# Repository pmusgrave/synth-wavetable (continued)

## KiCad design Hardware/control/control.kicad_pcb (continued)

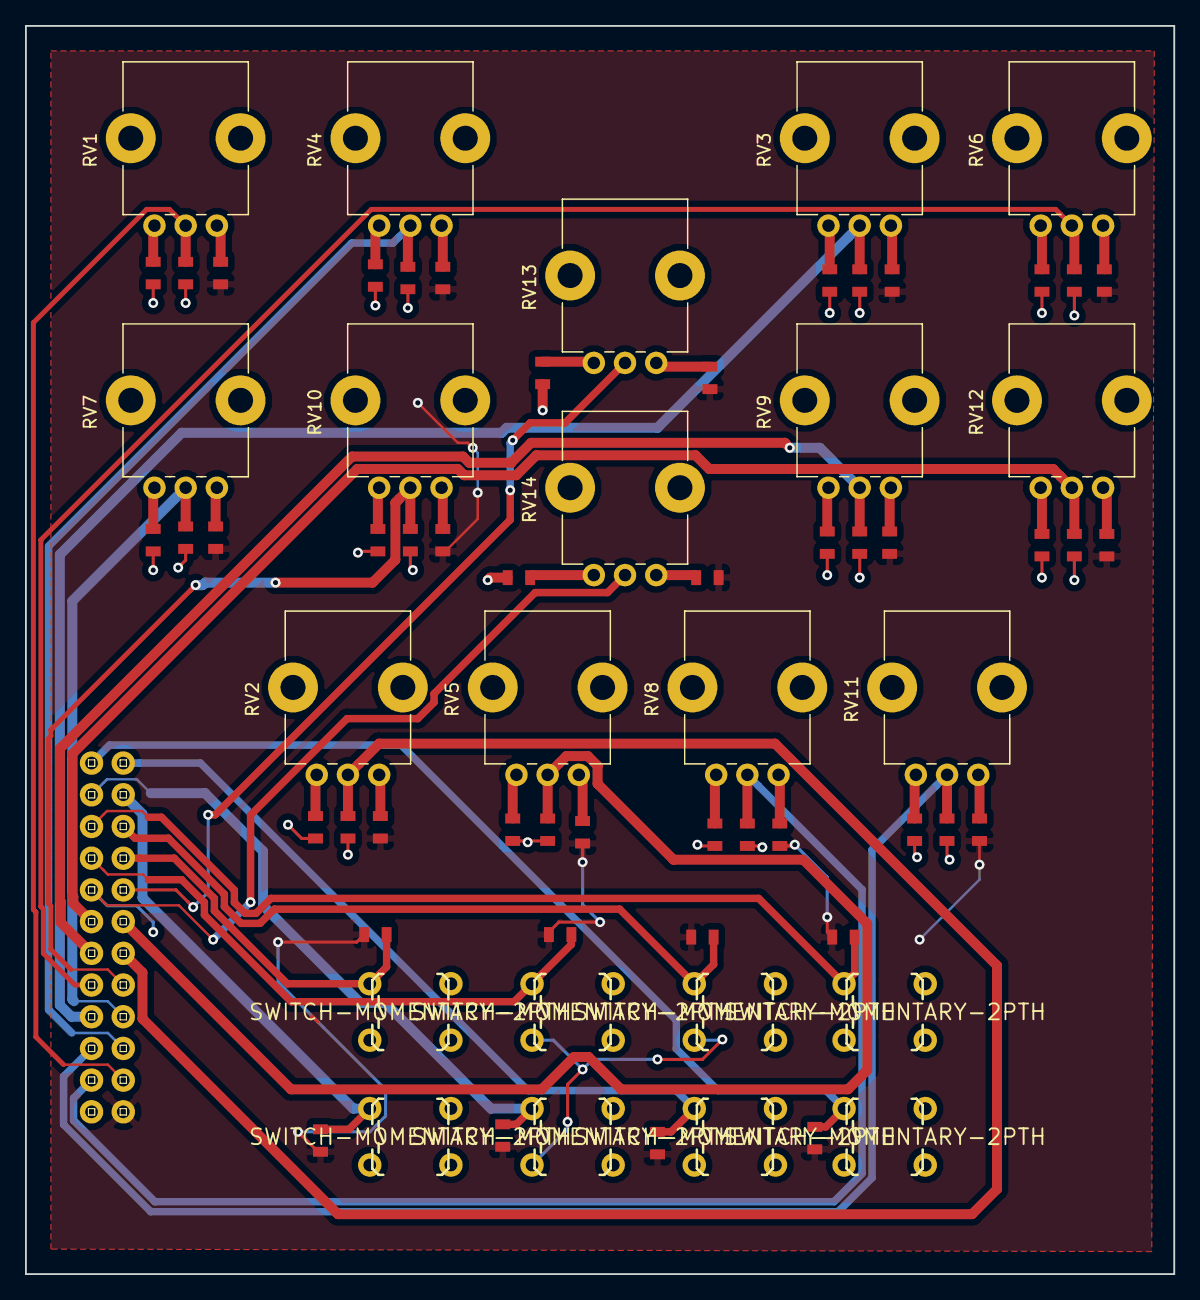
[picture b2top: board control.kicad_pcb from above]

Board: 2 copper layers, 92.0 x 100.0 mm, 71 parts (0 on the bottom side), 52 nets.

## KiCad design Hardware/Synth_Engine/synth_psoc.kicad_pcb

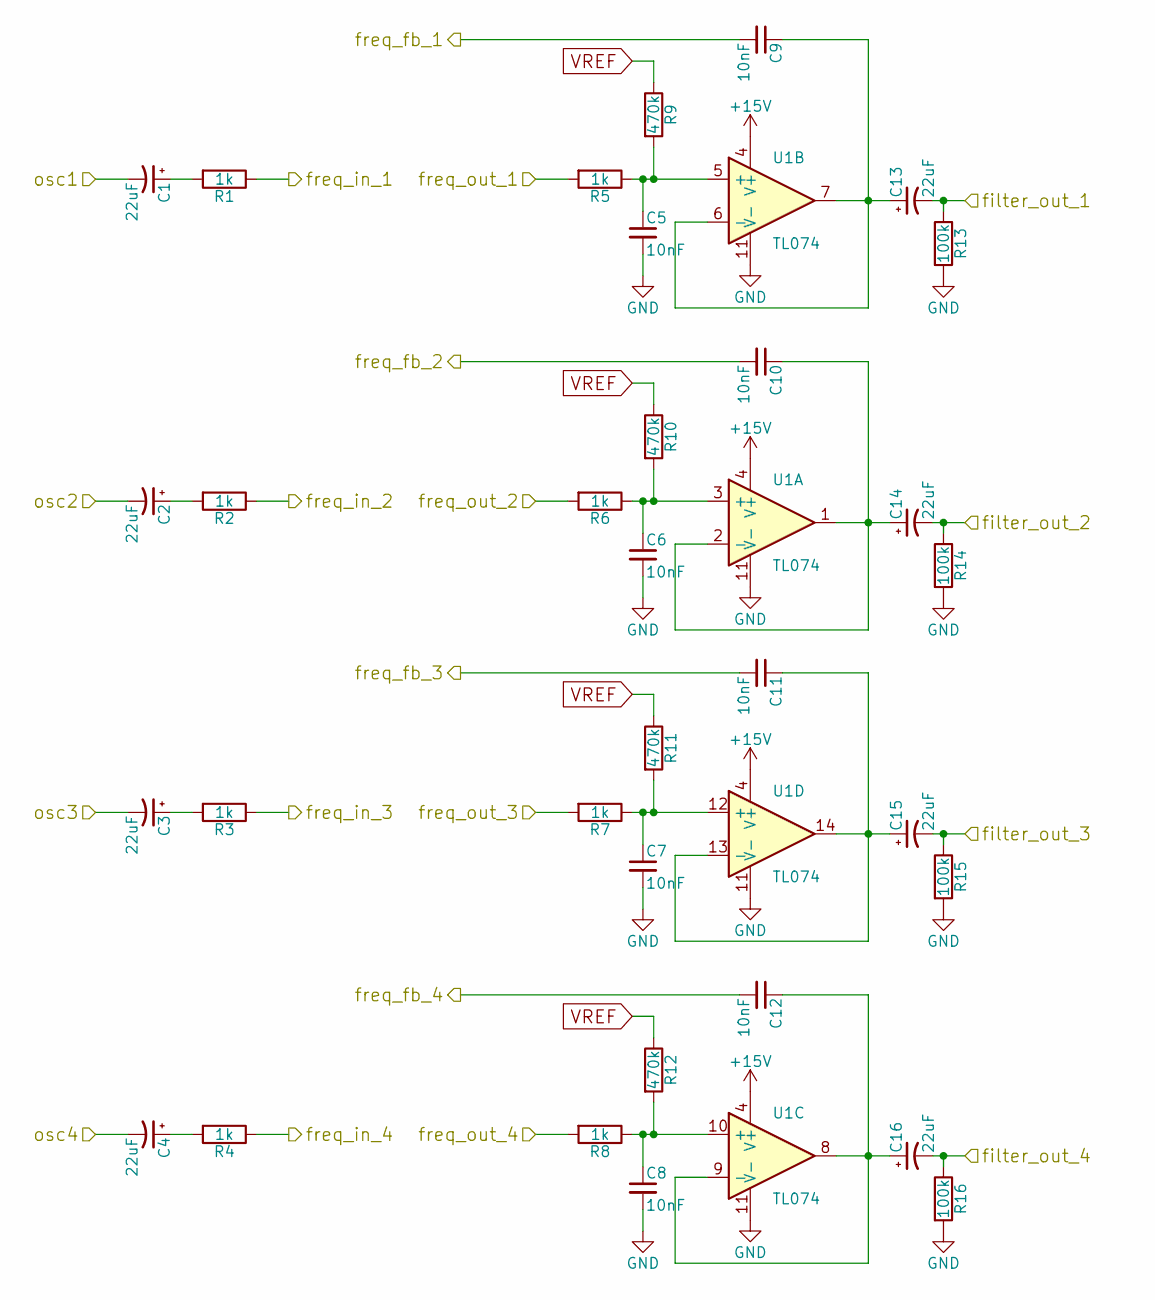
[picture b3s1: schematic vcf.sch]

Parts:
C1, C2, C3, C4, C13, C14, C15, C16: 22uF; CP_Elec_5x5.7
C5, C6, C7, C8, C9, C10, C11, C12: 10nF; 0805
R1, R2, R3, R4, R5, R6, R7, R8: 1k; 0805
R9, R10, R11, R12: 470k; 0805
R13, R14, R15, R16: 100k; 0805
U1: TL074; SOIC-14_W3.9mm

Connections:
+15V: U1.4 (V+); also elsewhere on the board
/Connectors/freq_fb_1: C9.2; also elsewhere on the board
/Connectors/freq_fb_2: C10.2; also elsewhere on the board
/Connectors/freq_fb_3: C11.2; also elsewhere on the board
/Connectors/freq_fb_4: C12.2; also elsewhere on the board
/Connectors/freq_in_1: R1.1; also elsewhere on the board
/Connectors/freq_in_2: R2.1; also elsewhere on the board
/Connectors/freq_in_3: R3.1; also elsewhere on the board
/Connectors/freq_in_4: R4.1; also elsewhere on the board
/Connectors/freq_out_1: R5.2; also elsewhere on the board
/Connectors/freq_out_2: R6.2; also elsewhere on the board
/Connectors/freq_out_3: R7.2; also elsewhere on the board
/Connectors/freq_out_4: R8.2; also elsewhere on the board
/Filters/filter_out_1: C13.2, R13.1; also elsewhere on the board
/Filters/filter_out_2: C14.2, R14.1; also elsewhere on the board
/Filters/filter_out_3: C15.2, R15.1; also elsewhere on the board
/Filters/filter_out_4: C16.2, R16.1; also elsewhere on the board
/Filters/osc1: C1.2; also elsewhere on the board
/Filters/osc2: C2.2; also elsewhere on the board
/Filters/osc3: C3.2; also elsewhere on the board
/Filters/osc4: C4.2; also elsewhere on the board
GND: C5.2, C6.2, C7.2, C8.2, R13.2, R14.2, R15.2, R16.2, U1.11 (V-); also elsewhere on the board
unnamed: C1.1, R1.2
unnamed: C2.1, R2.2
unnamed: C3.1, R3.2
unnamed: C4.1, R4.2
unnamed: C5.1, R5.1, R9.2, U1.5 (+)
unnamed: C6.1, R6.1, R10.2, U1.3 (+)
unnamed: C7.1, R7.1, R11.2, U1.12 (+)
unnamed: C8.1, R8.1, R12.2, U1.10 (+)
unnamed: C10.1, C14.1, U1.1, U1.2 (-)
unnamed: C11.1, C15.1, U1.13 (-), U1.14
unnamed: C12.1, C16.1, U1.8, U1.9 (-)
unnamed: C9.1, C13.1, U1.6 (-), U1.7
VREF: R9.1, R10.1, R11.1, R12.1; also elsewhere on the board

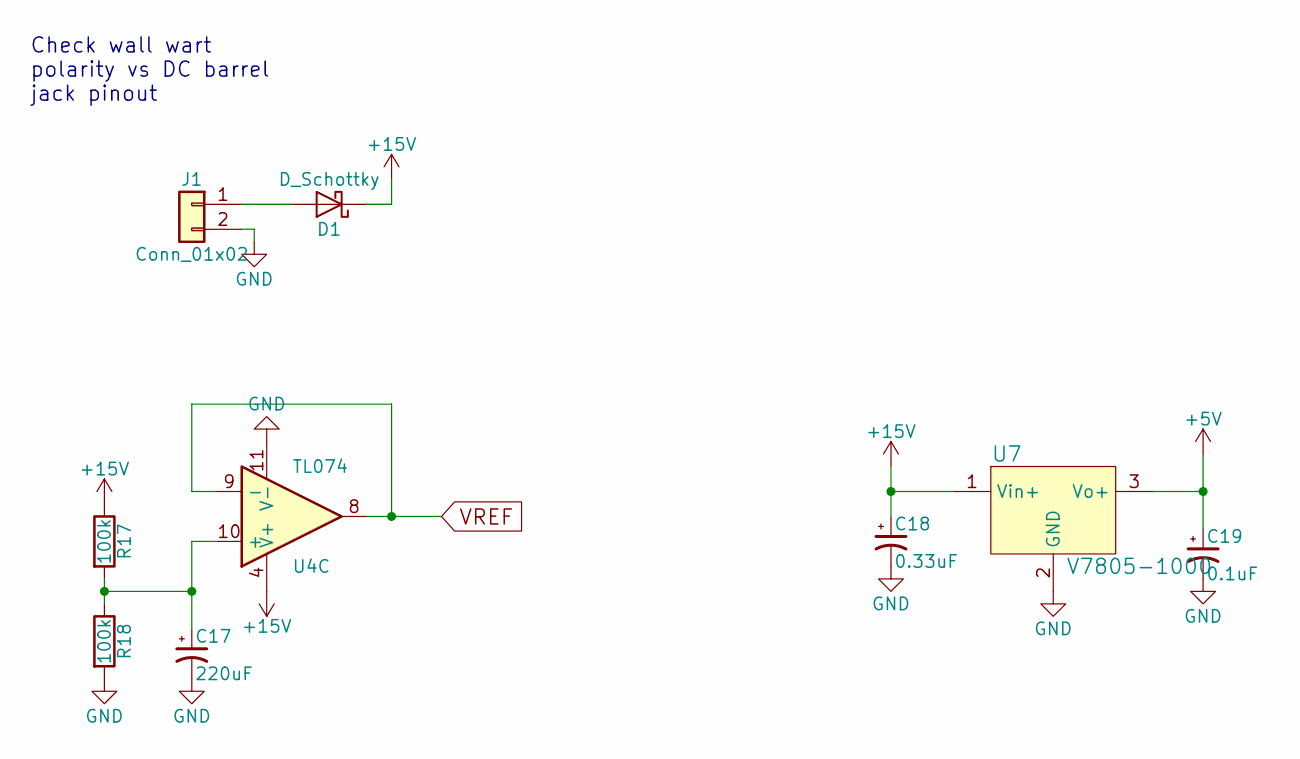
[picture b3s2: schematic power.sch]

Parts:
C17: 220uF; CP_Elec_8x10
C18: 0.33uF; 0805
C19: 0.1uF; 0805
D1: D_Schottky; D_SMB
J1: Conn_01x02; Pin_Header_Straight_1x02_Pitch2.00mm
R17, R18: 100k; 0805
U4: TL074; SOIC-14_W3.9mm
U7: V7805-1000; 3-SIP_Module_V7805-1000; MPN V7805-1000; Digi-Key_PN 102-1715-ND

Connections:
+5V: C19.1, U7.3 (Vo+); also elsewhere on the board
+15V: C18.1, D1.1 (K), R17.1, U4.4 (V+), U7.1 (Vin+); also elsewhere on the board
GND: C17.2, C18.2, C19.2, J1.2, R18.2, U4.11 (V-), U7.2 (GND); also elsewhere on the board
unnamed: C17.1, R17.2, R18.1, U4.10 (+)
unnamed: D1.2 (A), J1.1
VREF: U4.8, U4.9 (-); also elsewhere on the board

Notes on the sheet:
Check wall wart polarity vs DC barrel jack pinout

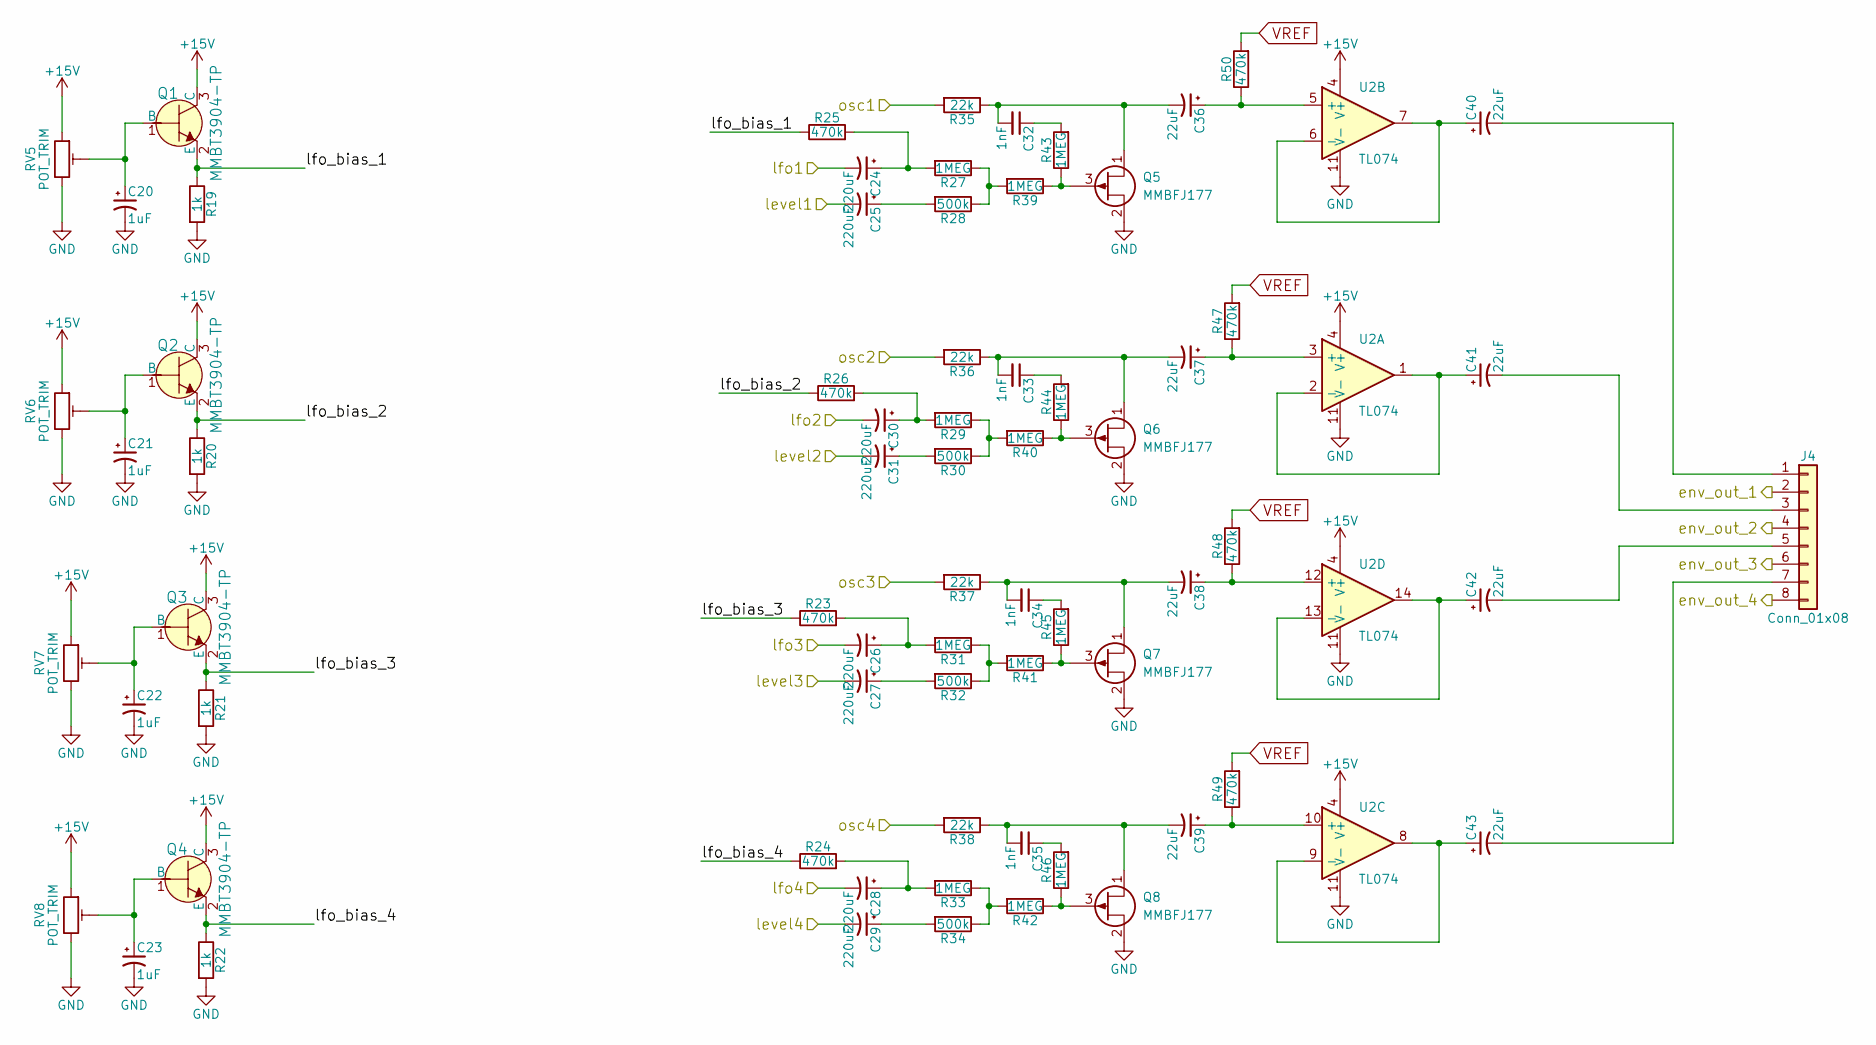
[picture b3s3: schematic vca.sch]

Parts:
C20, C21, C22, C23: 1uF; CP_Elec_4x4.5
C24, C25, C26, C27, C28, C29, C30, C31: 220uF; CP_Elec_8x10
C32, C33, C34, C35: 1nF; 0805
C36, C37, C38, C39, C40, C41, C42, C43: 22uF; CP_Elec_5x5.7
J4: Conn_01x08; Pin_Header_Straight_1x08_Pitch2.54mm
Q1, Q2, Q3, Q4: MMBT3904-TP; SOT-23-3; MPN MMBT3904-TP; Digi-Key_PN MMBT3904TPMSCT-ND
Q5, Q6, Q7, Q8: MMBFJ177; SOT-23-3
R19, R20, R21, R22: 1k; 0805
R23, R24, R25, R26, R47, R48, R49, R50: 470k; 0805
R27, R29, R31, R33, R39, R40, R41, R42, R43, R44, R45, R46: 1MEG; 0805
R28, R30, R32, R34: 500k; 0805
R35, R36, R37, R38: 22k; 0805
RV5, RV6, RV7, RV8: POT_TRIM; Potentiometer_Trimmer-EVM3E
U2: TL074; SOIC-14_W3.9mm

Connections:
+15V: Q1.3 (C), Q2.3 (C), Q3.3 (C), Q4.3 (C), RV5.1, RV6.1, RV7.1, RV8.1, U2.4 (V+); also elsewhere on the board
/Envelope/env_out_1: J4.2; also elsewhere on the board
/Envelope/env_out_2: J4.4; also elsewhere on the board
/Envelope/env_out_3: J4.6; also elsewhere on the board
/Envelope/env_out_4: J4.8; also elsewhere on the board
/Envelope/lfo_bias_1: Q1.2 (E), R19.1, R25.1
/Envelope/lfo_bias_2: Q2.2 (E), R20.1, R26.1
/Envelope/lfo_bias_3: Q3.2 (E), R21.1, R23.1
/Envelope/lfo_bias_4: Q4.2 (E), R22.1, R24.1
/Filters/filter_out_1: R35.2; also elsewhere on the board
/Filters/filter_out_2: R36.2; also elsewhere on the board
/Filters/filter_out_3: R37.2; also elsewhere on the board
/Filters/filter_out_4: R38.2; also elsewhere on the board
/Microcontroller/envelope_pwm_1: C25.2; also elsewhere on the board
/Microcontroller/envelope_pwm_2: C31.2; also elsewhere on the board
/Microcontroller/envelope_pwm_3: C27.2; also elsewhere on the board
/Microcontroller/envelope_pwm_4: C29.2; also elsewhere on the board
/lfo_out_1: C24.2; also elsewhere on the board
/lfo_out_2: C30.2; also elsewhere on the board
/lfo_out_3: C26.2; also elsewhere on the board
/lfo_out_4: C28.2; also elsewhere on the board
GND: C20.2, C21.2, C22.2, C23.2, Q5.2 (S), Q6.2 (S), Q7.2 (S), Q8.2 (S), R19.2, R20.2, R21.2, R22.2, RV5.3, RV6.3, RV7.3, RV8.3, U2.11 (V-); also elsewhere on the board
unnamed: C20.1, Q1.1 (B), RV5.2
unnamed: C21.1, Q2.1 (B), RV6.2
unnamed: C22.1, Q3.1 (B), RV7.2
unnamed: C23.1, Q4.1 (B), RV8.2
unnamed: C24.1, R25.2, R27.2
unnamed: C25.1, R28.2
unnamed: C26.1, R23.2, R31.2
unnamed: C27.1, R32.2
unnamed: C28.1, R24.2, R33.2
unnamed: C29.1, R34.2
unnamed: C30.1, R26.2, R29.2
unnamed: C31.1, R30.2
unnamed: C32.1, R43.2
unnamed: C32.2, C36.2, Q5.1 (D), R35.1
unnamed: C33.1, R44.2
unnamed: C33.2, C37.2, Q6.1 (D), R36.1
unnamed: C34.1, R45.2
unnamed: C34.2, C38.2, Q7.1 (D), R37.1
unnamed: C35.1, R46.2
unnamed: C35.2, C39.2, Q8.1 (D), R38.1
unnamed: C36.1, R50.1, U2.5 (+)
unnamed: C37.1, R47.1, U2.3 (+)
unnamed: C38.1, R48.1, U2.12 (+)
unnamed: C39.1, R49.1, U2.10 (+)
unnamed: C40.1, U2.6 (-), U2.7
unnamed: C40.2, J4.1
unnamed: C41.1, U2.1, U2.2 (-)
unnamed: C41.2, J4.3
unnamed: C42.1, U2.13 (-), U2.14
unnamed: C42.2, J4.5
unnamed: C43.1, U2.8, U2.9 (-)
unnamed: C43.2, J4.7
unnamed: Q5.3 (G), R39.1, R43.1
unnamed: Q6.3 (G), R40.1, R44.1
unnamed: Q7.3 (G), R41.1, R45.1
unnamed: Q8.3 (G), R42.1, R46.1
unnamed: R27.1, R28.1, R39.2
unnamed: R29.1, R30.1, R40.2
unnamed: R31.1, R32.1, R41.2
unnamed: R33.1, R34.1, R42.2
VREF: R47.2, R48.2, R49.2, R50.2; also elsewhere on the board

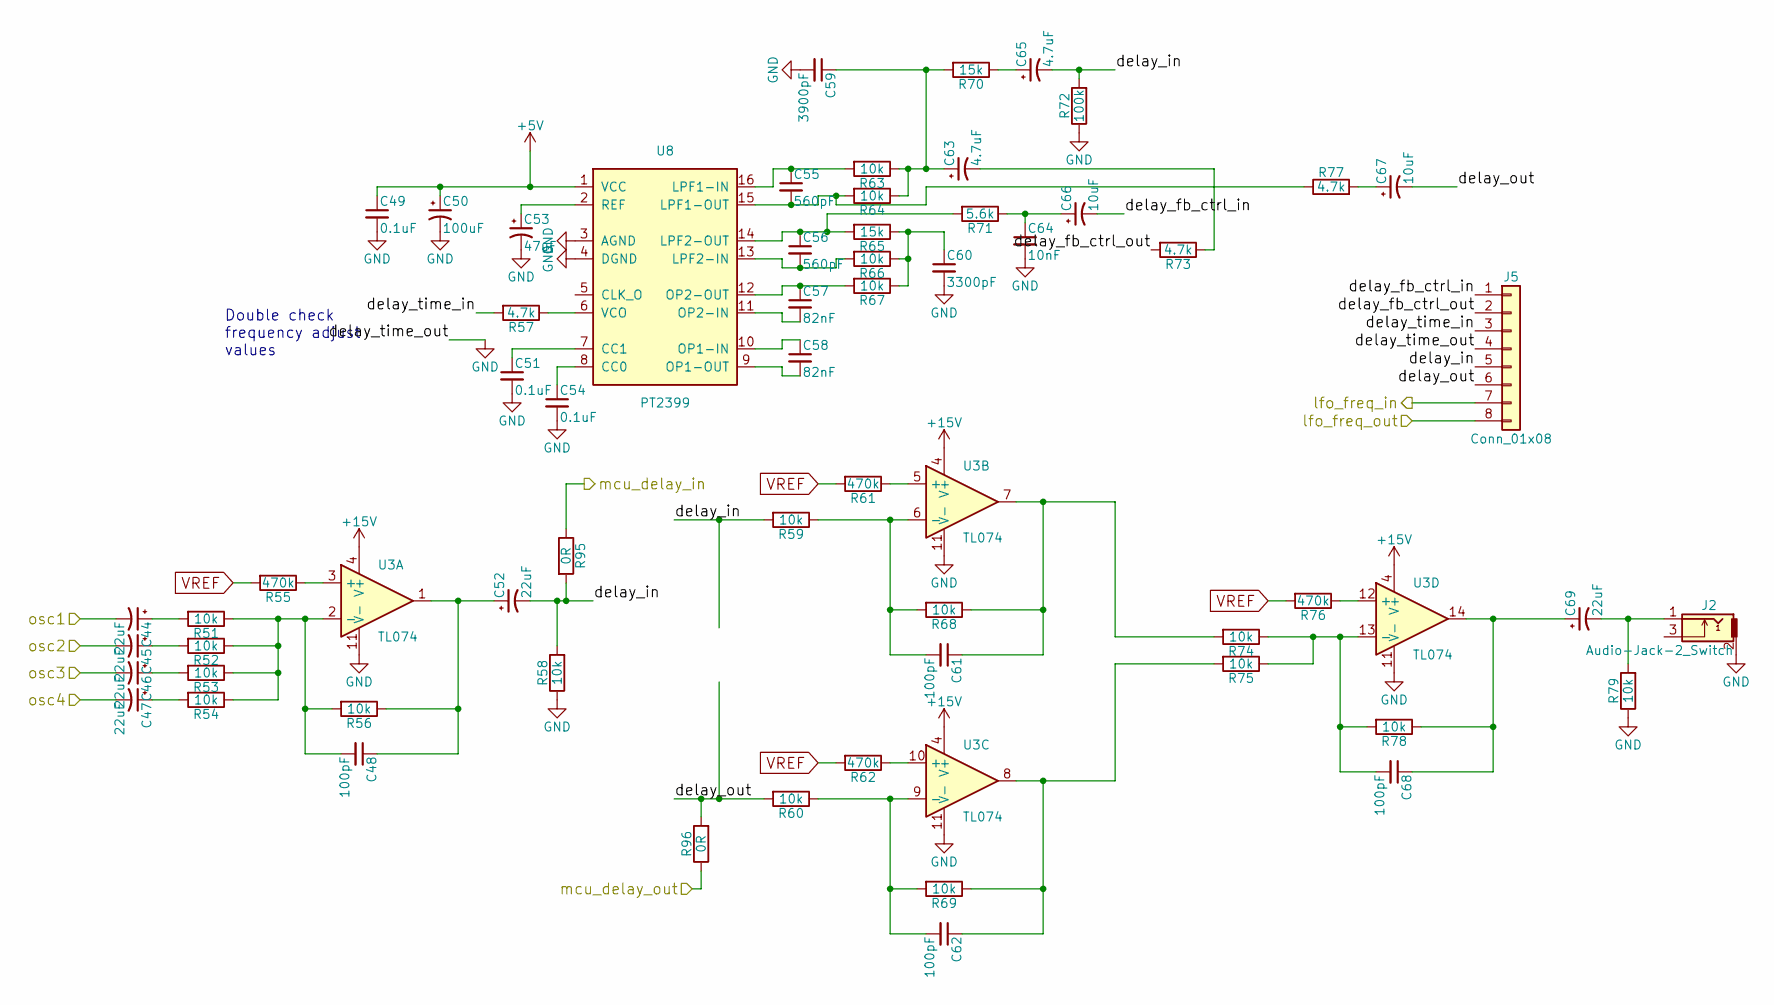
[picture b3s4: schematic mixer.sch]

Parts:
C44, C45, C46, C47, C52, C69: 22uF; CP_Elec_5x5.7
C48, C61, C62, C68: 100pF; 0805
C49, C51, C54: 0.1uF; 0805
C50: 100uF; CP_Elec_5x5.7
C53: 47uF; CP_Elec_4x5.7
C55, C56: 560pF; 0805
C57, C58: 82nF; 0805
C59: 3900pF; 0805
C60: 3300pF; 0805
C63, C65: 4.7uF; CP_Elec_4x5.7
C64: 10nF; 0805
C66, C67: 10uF; CP_Elec_4x5.7
J2: Audio-Jack-2_Switch; Pin_Header_Straight_1x03_Pitch2.00mm
J5: Conn_01x08; Pin_Header_Straight_1x08_Pitch2.54mm
R51, R52, R53, R54, R56, R58, R59, R60, R63, R64, R66, R67, R68, R69, R74, R75, R78, R79: 10k; 0805
R55, R61, R62, R76: 470k; 0805
R57, R73, R77: 4.7k; 0805
R65, R70: 15k; 0805
R71: 5.6k; 0805
R72: 100k; 0805
R95, R96: 0R; 0805
U3: TL074; SOIC-14_W3.9mm
U8: PT2399; DIP-16_W7.62mm

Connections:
+5V: C49.1, C50.1, U8.1 (VCC); also elsewhere on the board
+15V: U3.4 (V+); also elsewhere on the board
/Envelope/env_out_1: C44.2; also elsewhere on the board
/Envelope/env_out_2: C45.2; also elsewhere on the board
/Envelope/env_out_3: C46.2; also elsewhere on the board
/Envelope/env_out_4: C47.2; also elsewhere on the board
/Mixer and Effects/delay_fb_ctrl_in: C66.2, J5.1
/Mixer and Effects/delay_fb_ctrl_out: J5.2, R73.2
/Mixer and Effects/delay_in: C52.2, C65.2, J5.5, R58.2, R59.2, R72.2, R95.2
/Mixer and Effects/delay_out: C67.2, J5.6, R60.2, R96.2
/Mixer and Effects/delay_time_in: J5.3, R57.2
/lfo_freq_in: J5.7; also elsewhere on the board
/lfo_freq_out: J5.8; also elsewhere on the board
/mcu_delay_in: R95.1; also elsewhere on the board
/mcu_delay_out: R96.1; also elsewhere on the board
GND: C49.2, C50.2, C51.2, C53.2, C54.2, C59.2, C60.2, C64.2, J2.2, J5.4, R58.1, R72.1, R79.1, U3.11 (V-), U8.3 (AGND), U8.4 (DGND); also elsewhere on the board
unnamed: C44.1, R51.2
unnamed: C45.1, R52.2
unnamed: C46.1, R53.2
unnamed: C47.1, R54.2
unnamed: C48.1, C52.1, R56.1, U3.1
unnamed: C48.2, R51.1, R52.1, R53.1, R54.1, R56.2, U3.2 (-)
unnamed: C51.1, U8.7 (CC1)
unnamed: C53.1, U8.2 (REF)
unnamed: C54.1, U8.8 (CC0)
unnamed: C55.1, R63.2, U8.16 (LPF1-IN)
unnamed: C55.2, R64.2, R77.1, U8.15 (LPF1-OUT)
unnamed: C56.1, R65.2, R71.2, U8.14 (LPF2-OUT)
unnamed: C56.2, R66.2, U8.13 (LPF2-IN)
unnamed: C57.1, R67.2, U8.12 (OP2-OUT)
unnamed: C57.2, U8.11 (OP2-IN)
unnamed: C58.1, U8.10 (OP1-IN)
unnamed: C58.2, U8.9 (OP1-OUT)
unnamed: C59.1, C63.1, R63.1, R64.1, R70.2
unnamed: C60.1, R65.1, R66.1, R67.1
unnamed: C61.1, R68.1, R74.2, U3.7
unnamed: C61.2, R59.1, R68.2, U3.6 (-)
unnamed: C62.1, R69.1, R75.2, U3.8
unnamed: C62.2, R60.1, R69.2, U3.9 (-)
unnamed: C63.2, R73.1
unnamed: C64.1, C66.1, R71.1
unnamed: C65.1, R70.1
unnamed: C67.1, R77.2
unnamed: C68.1, C69.1, R78.1, U3.14
unnamed: C68.2, R74.1, R75.1, R78.2, U3.13 (-)
unnamed: C69.2, J2.1, R79.2
unnamed: R55.1, U3.3 (+)
unnamed: R57.1, U8.6 (VCO)
unnamed: R61.1, U3.5 (+)
unnamed: R62.1, U3.10 (+)
unnamed: R76.1, U3.12 (+)
VREF: R55.2, R61.2, R62.2, R76.2; also elsewhere on the board

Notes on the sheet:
Double check frequency adjust values

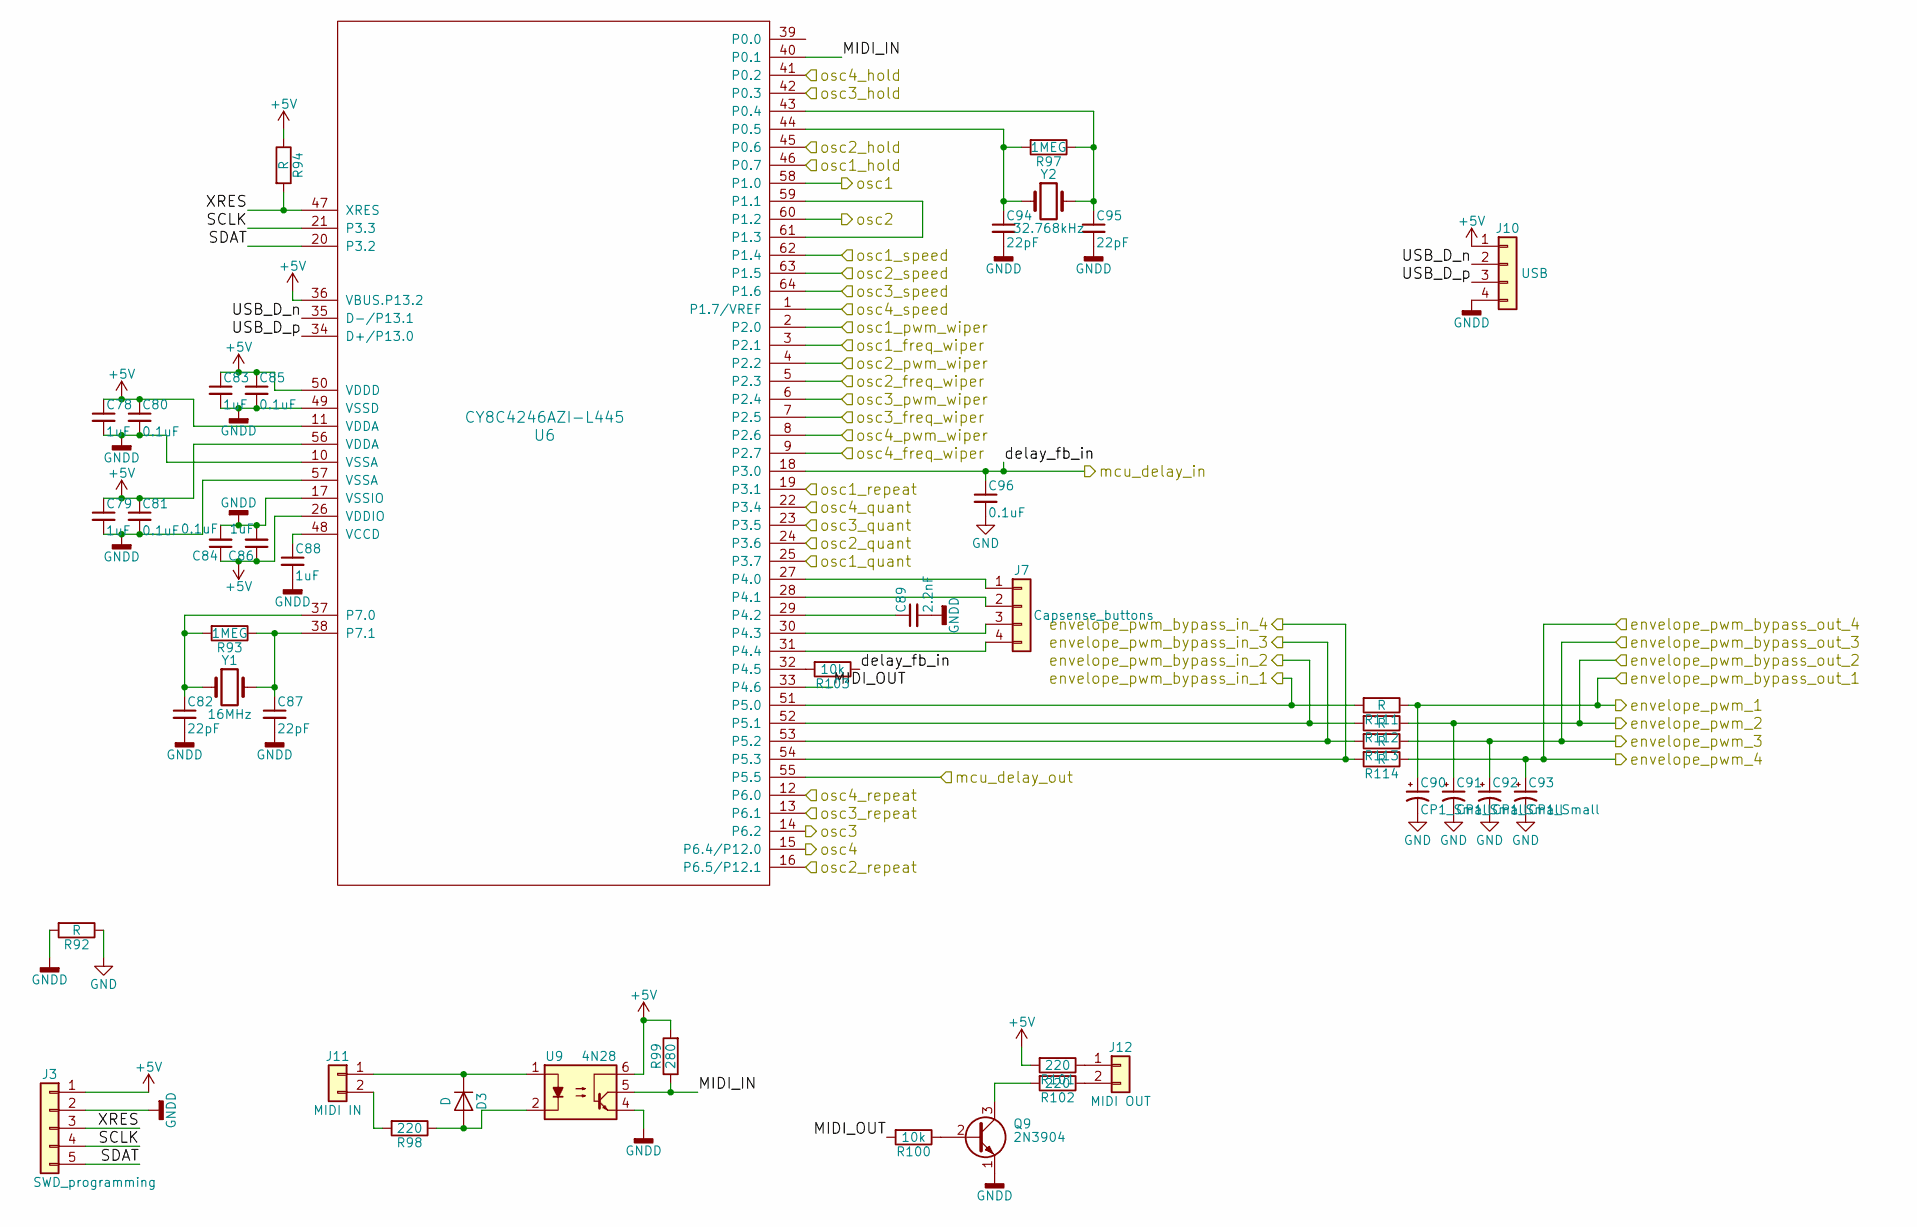
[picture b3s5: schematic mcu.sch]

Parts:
C78, C79, C83, C86, C88: 1uF; 0805
C80, C81, C84, C85, C96: 0.1uF; 0805
C82, C87, C94, C95: 22pF; 0805
C89: 2.2nF; 0805
C90, C91, C92, C93: CP1_Small; CP_Elec_5x5.7
D3: D; SOT-23-3
J3: SWD_programming; Pin_Header_Straight_1x05_Pitch2.54mm
J7: Capsense_buttons; Pin_Header_Straight_1x04_Pitch2.00mm
J10: USB; Pin_Header_Straight_1x04_Pitch2.00mm
J11: MIDI IN; Pin_Header_Straight_1x02_Pitch2.00mm
J12: MIDI OUT; Pin_Header_Straight_1x02_Pitch2.00mm
Q9: 2N3904; SOT-23-3
R92, R94, R111, R112, R113, R114: R; 0805
R93, R97: 1MEG; 0805
R98, R101, R102: 220; 0805
R99: 280; 0805
R100, R103: 10k; 0805
U6: CY8C4246AZI-L445; LQFP-64_10x10mm
U9: 4N28; DIP-8_W7.62mm
Y1: 16MHz; Crystal_SMD_HC49-SD_HandSoldering
Y2: 32.768kHz; 1206

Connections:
+5V: C78.1, C79.1, C80.1, C81.1, C83.1, C84.1, C85.1, C86.1, J3.1, J10.1, R94.1, R99.2, R101.2, U6.11 (VDDA), U6.26 (VDDIO), U6.36 (VBUS.P13.2), U6.50 (VDDD), U6.56 (VDDA), U9.6; also elsewhere on the board
/Connectors/envelope_pwm_bypass_in_1: R111.2, U6.51 (P5.0); also elsewhere on the board
/Connectors/envelope_pwm_bypass_in_2: R112.2, U6.52 (P5.1); also elsewhere on the board
/Connectors/envelope_pwm_bypass_in_3: R113.2, U6.53 (P5.2); also elsewhere on the board
/Connectors/envelope_pwm_bypass_in_4: R114.2, U6.54 (P5.3); also elsewhere on the board
/Connectors/osc1_freq_wiper: U6.3 (P2.1); also elsewhere on the board
/Connectors/osc1_hold: U6.46 (P0.7); also elsewhere on the board
/Connectors/osc1_pwm_wiper: U6.2 (P2.0); also elsewhere on the board
/Connectors/osc1_quant: U6.25 (P3.7); also elsewhere on the board
/Connectors/osc1_repeat: U6.19 (P3.1); also elsewhere on the board
/Connectors/osc1_speed: U6.62 (P1.4); also elsewhere on the board
/Connectors/osc2_freq_wiper: U6.5 (P2.3); also elsewhere on the board
/Connectors/osc2_hold: U6.45 (P0.6); also elsewhere on the board
/Connectors/osc2_pwm_wiper: U6.4 (P2.2); also elsewhere on the board
/Connectors/osc2_quant: U6.24 (P3.6); also elsewhere on the board
/Connectors/osc2_repeat: U6.16 (P6.5/P12.1); also elsewhere on the board
/Connectors/osc2_speed: U6.63 (P1.5); also elsewhere on the board
/Connectors/osc3_freq_wiper: U6.7 (P2.5); also elsewhere on the board
/Connectors/osc3_hold: U6.42 (P0.3); also elsewhere on the board
/Connectors/osc3_pwm_wiper: U6.6 (P2.4); also elsewhere on the board
/Connectors/osc3_quant: U6.23 (P3.5); also elsewhere on the board
/Connectors/osc3_repeat: U6.13 (P6.1); also elsewhere on the board
/Connectors/osc3_speed: U6.64 (P1.6); also elsewhere on the board
/Connectors/osc4_freq_wiper: U6.9 (P2.7); also elsewhere on the board
/Connectors/osc4_hold: U6.41 (P0.2); also elsewhere on the board
/Connectors/osc4_pwm_wiper: U6.8 (P2.6); also elsewhere on the board
/Connectors/osc4_quant: U6.22 (P3.4); also elsewhere on the board
/Connectors/osc4_repeat: U6.12 (P6.0); also elsewhere on the board
/Connectors/osc4_speed: U6.1 (P1.7/VREF); also elsewhere on the board
/Filters/osc1: U6.58 (P1.0); also elsewhere on the board
/Filters/osc2: U6.60 (P1.2); also elsewhere on the board
/Filters/osc3: U6.14 (P6.2); also elsewhere on the board
/Filters/osc4: U6.15 (P6.4/P12.0); also elsewhere on the board
/Microcontroller/MIDI_IN: R99.1, U6.40 (P0.1), U9.5
/Microcontroller/MIDI_OUT: R100.2, U6.33 (P4.6)
/Microcontroller/SCLK: J3.4, U6.21 (P3.3)
/Microcontroller/SDAT: J3.5, U6.20 (P3.2)
/Microcontroller/USB_D_n: J10.2, U6.35 (D-/P13.1)
/Microcontroller/USB_D_p: J10.3, U6.34 (D+/P13.0)
/Microcontroller/XRES: J3.3, R94.2, U6.47 (XRES)
/Microcontroller/envelope_pwm_1: C90.1, R111.1; also elsewhere on the board
/Microcontroller/envelope_pwm_2: C91.1, R112.1; also elsewhere on the board
/Microcontroller/envelope_pwm_3: C92.1, R113.1; also elsewhere on the board
/Microcontroller/envelope_pwm_4: C93.1, R114.1; also elsewhere on the board
/mcu_delay_in: C96.1, R103.1, U6.18 (P3.0); also elsewhere on the board
/mcu_delay_out: U6.55 (P5.5); also elsewhere on the board
GND: C90.2, C91.2, C92.2, C93.2, C96.2, R92.1; also elsewhere on the board
GNDD: C78.2, C79.2, C80.2, C81.2, C82.2, C83.2, C84.2, C85.2, C86.2, C87.2, C88.2, C89.2, C94.2, C95.2, J3.2, J10.4, Q9.1 (E), R92.2, U6.10 (VSSA), U6.17 (VSSIO), U6.49 (VSSD), U6.57 (VSSA), U9.4
unnamed: C82.1, R93.2, U6.37 (P7.0), Y1.1
unnamed: C87.1, R93.1, U6.38 (P7.1), Y1.2
unnamed: C88.1, U6.48 (VCCD)
unnamed: C89.1, U6.29 (P4.2)
unnamed: C94.1, R97.2, U6.44 (P0.5), Y2.1
unnamed: C95.1, R97.1, U6.43 (P0.4), Y2.2
unnamed: D3.1 (K), J11.1, U9.1
unnamed: D3.2 (A), R98.1, U9.2
unnamed: J7.1, U6.27 (P4.0)
unnamed: J7.2, U6.28 (P4.1)
unnamed: J7.3, U6.30 (P4.3)
unnamed: J7.4, U6.31 (P4.4)
unnamed: J11.2, R98.2
unnamed: J12.1, R101.1
unnamed: J12.2, R102.1
unnamed: Q9.2 (B), R100.1
unnamed: Q9.3 (C), R102.2
unnamed: R103.2, U6.32 (P4.5)
unnamed: U6.59 (P1.1), U6.61 (P1.3)

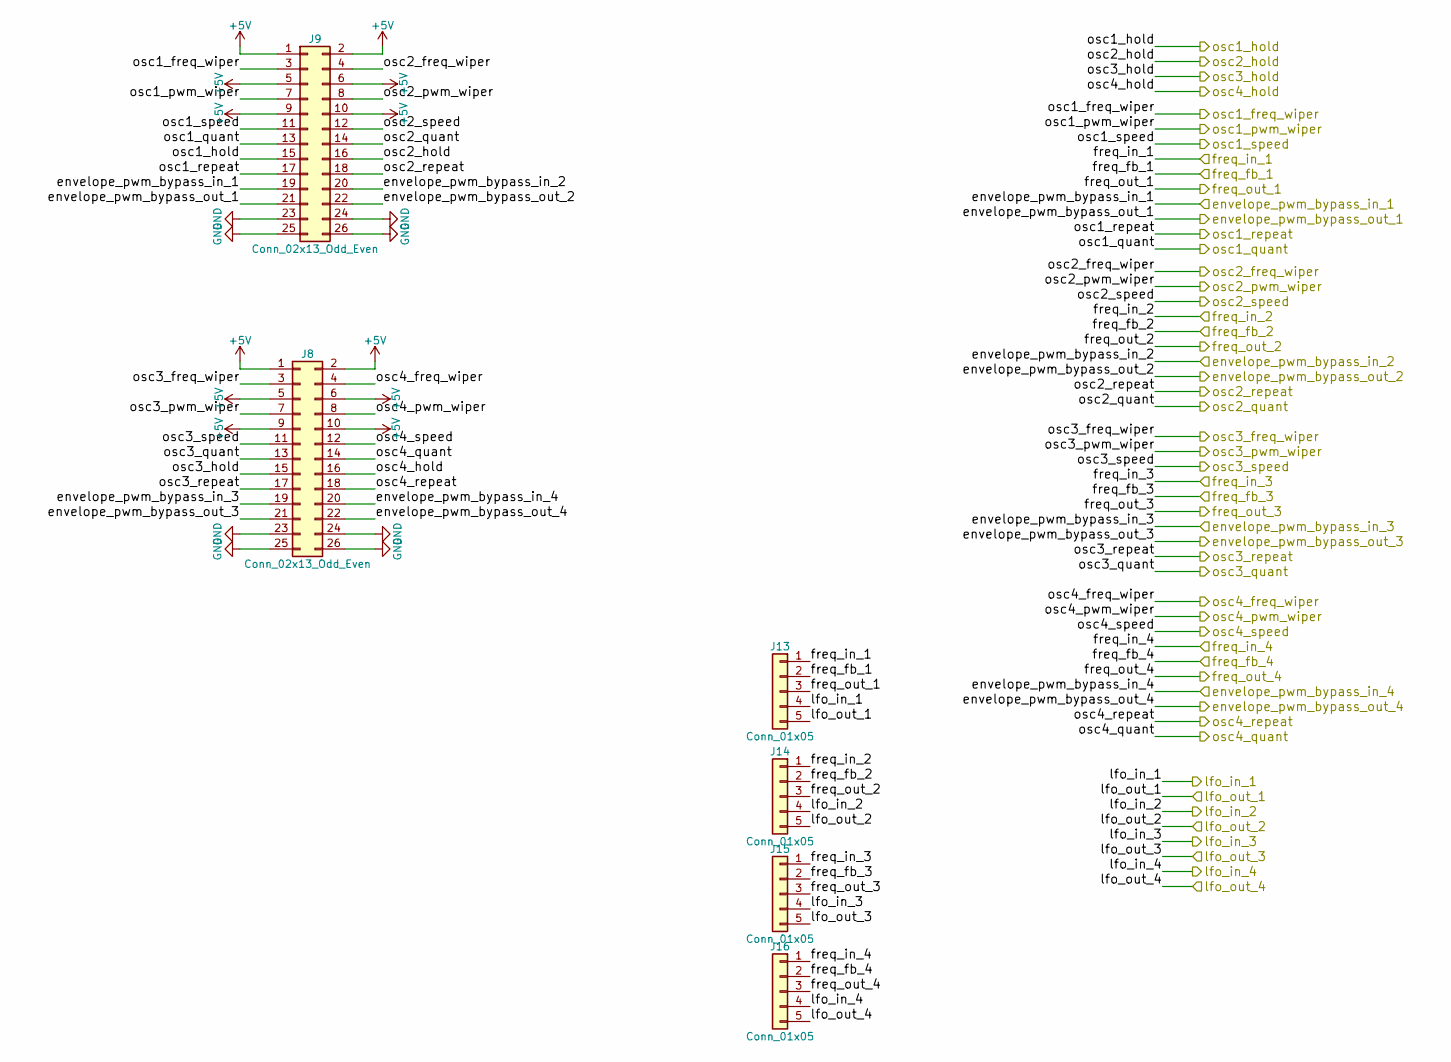
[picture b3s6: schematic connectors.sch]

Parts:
J8, J9: Conn_02x13_Odd_Even; Pin_Header_Straight_2x13_Pitch2.54mm
J13, J14, J15, J16: Conn_01x05; Pin_Header_Straight_1x05_Pitch2.54mm

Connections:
+5V: J8.1, J8.2, J8.5, J8.6, J8.9, J8.10, J9.1, J9.2, J9.5, J9.6, J9.9, J9.10; also elsewhere on the board
/Connectors/envelope_pwm_bypass_in_1: J9.19; also elsewhere on the board
/Connectors/envelope_pwm_bypass_in_2: J9.20; also elsewhere on the board
/Connectors/envelope_pwm_bypass_in_3: J8.19; also elsewhere on the board
/Connectors/envelope_pwm_bypass_in_4: J8.20; also elsewhere on the board
/Connectors/freq_fb_1: J13.2; also elsewhere on the board
/Connectors/freq_fb_2: J14.2; also elsewhere on the board
/Connectors/freq_fb_3: J15.2; also elsewhere on the board
/Connectors/freq_fb_4: J16.2; also elsewhere on the board
/Connectors/freq_in_1: J13.1; also elsewhere on the board
/Connectors/freq_in_2: J14.1; also elsewhere on the board
/Connectors/freq_in_3: J15.1; also elsewhere on the board
/Connectors/freq_in_4: J16.1; also elsewhere on the board
/Connectors/freq_out_1: J13.3; also elsewhere on the board
/Connectors/freq_out_2: J14.3; also elsewhere on the board
/Connectors/freq_out_3: J15.3; also elsewhere on the board
/Connectors/freq_out_4: J16.3; also elsewhere on the board
/Connectors/osc1_freq_wiper: J9.3; also elsewhere on the board
/Connectors/osc1_hold: J9.15; also elsewhere on the board
/Connectors/osc1_pwm_wiper: J9.7; also elsewhere on the board
/Connectors/osc1_quant: J9.13; also elsewhere on the board
/Connectors/osc1_repeat: J9.17; also elsewhere on the board
/Connectors/osc1_speed: J9.11; also elsewhere on the board
/Connectors/osc2_freq_wiper: J9.4; also elsewhere on the board
/Connectors/osc2_hold: J9.16; also elsewhere on the board
/Connectors/osc2_pwm_wiper: J9.8; also elsewhere on the board
/Connectors/osc2_quant: J9.14; also elsewhere on the board
/Connectors/osc2_repeat: J9.18; also elsewhere on the board
/Connectors/osc2_speed: J9.12; also elsewhere on the board
/Connectors/osc3_freq_wiper: J8.3; also elsewhere on the board
/Connectors/osc3_hold: J8.15; also elsewhere on the board
/Connectors/osc3_pwm_wiper: J8.7; also elsewhere on the board
/Connectors/osc3_quant: J8.13; also elsewhere on the board
/Connectors/osc3_repeat: J8.17; also elsewhere on the board
/Connectors/osc3_speed: J8.11; also elsewhere on the board
/Connectors/osc4_freq_wiper: J8.4; also elsewhere on the board
/Connectors/osc4_hold: J8.16; also elsewhere on the board
/Connectors/osc4_pwm_wiper: J8.8; also elsewhere on the board
/Connectors/osc4_quant: J8.14; also elsewhere on the board
/Connectors/osc4_repeat: J8.18; also elsewhere on the board
/Connectors/osc4_speed: J8.12; also elsewhere on the board
/Microcontroller/envelope_pwm_1: J9.21; also elsewhere on the board
/Microcontroller/envelope_pwm_2: J9.22; also elsewhere on the board
/Microcontroller/envelope_pwm_3: J8.21; also elsewhere on the board
/Microcontroller/envelope_pwm_4: J8.22; also elsewhere on the board
/lfo_in_1: J13.4; also elsewhere on the board
/lfo_in_2: J14.4; also elsewhere on the board
/lfo_in_3: J15.4; also elsewhere on the board
/lfo_in_4: J16.4; also elsewhere on the board
/lfo_out_1: J13.5; also elsewhere on the board
/lfo_out_2: J14.5; also elsewhere on the board
/lfo_out_3: J15.5; also elsewhere on the board
/lfo_out_4: J16.5; also elsewhere on the board
GND: J8.23, J8.24, J8.25, J8.26, J9.23, J9.24, J9.25, J9.26; also elsewhere on the board
